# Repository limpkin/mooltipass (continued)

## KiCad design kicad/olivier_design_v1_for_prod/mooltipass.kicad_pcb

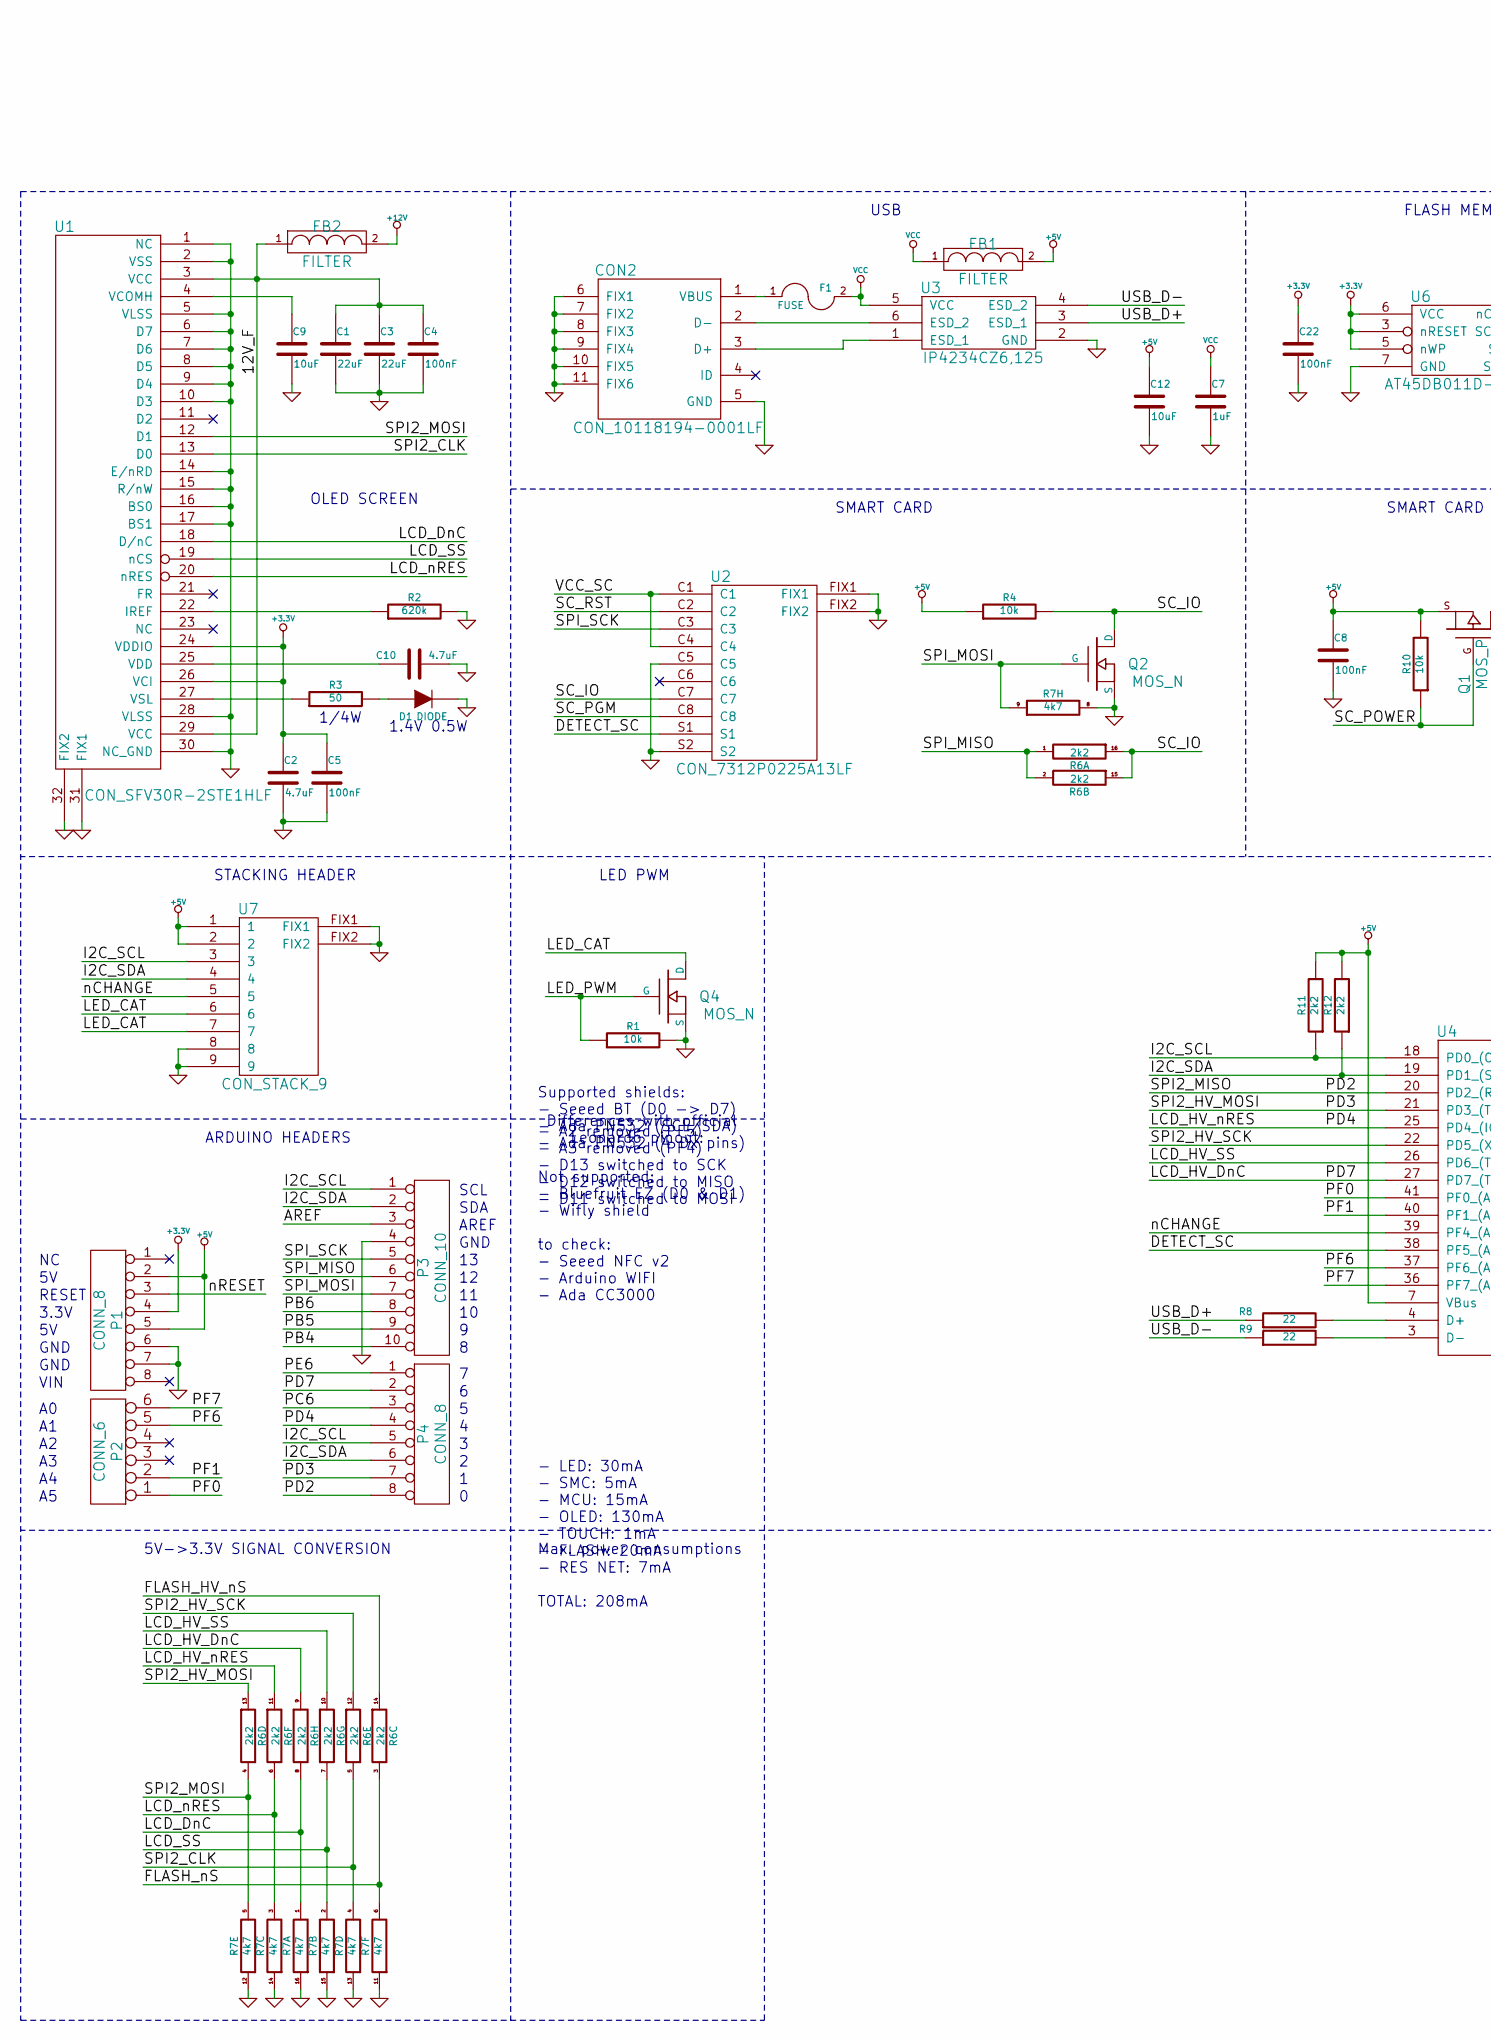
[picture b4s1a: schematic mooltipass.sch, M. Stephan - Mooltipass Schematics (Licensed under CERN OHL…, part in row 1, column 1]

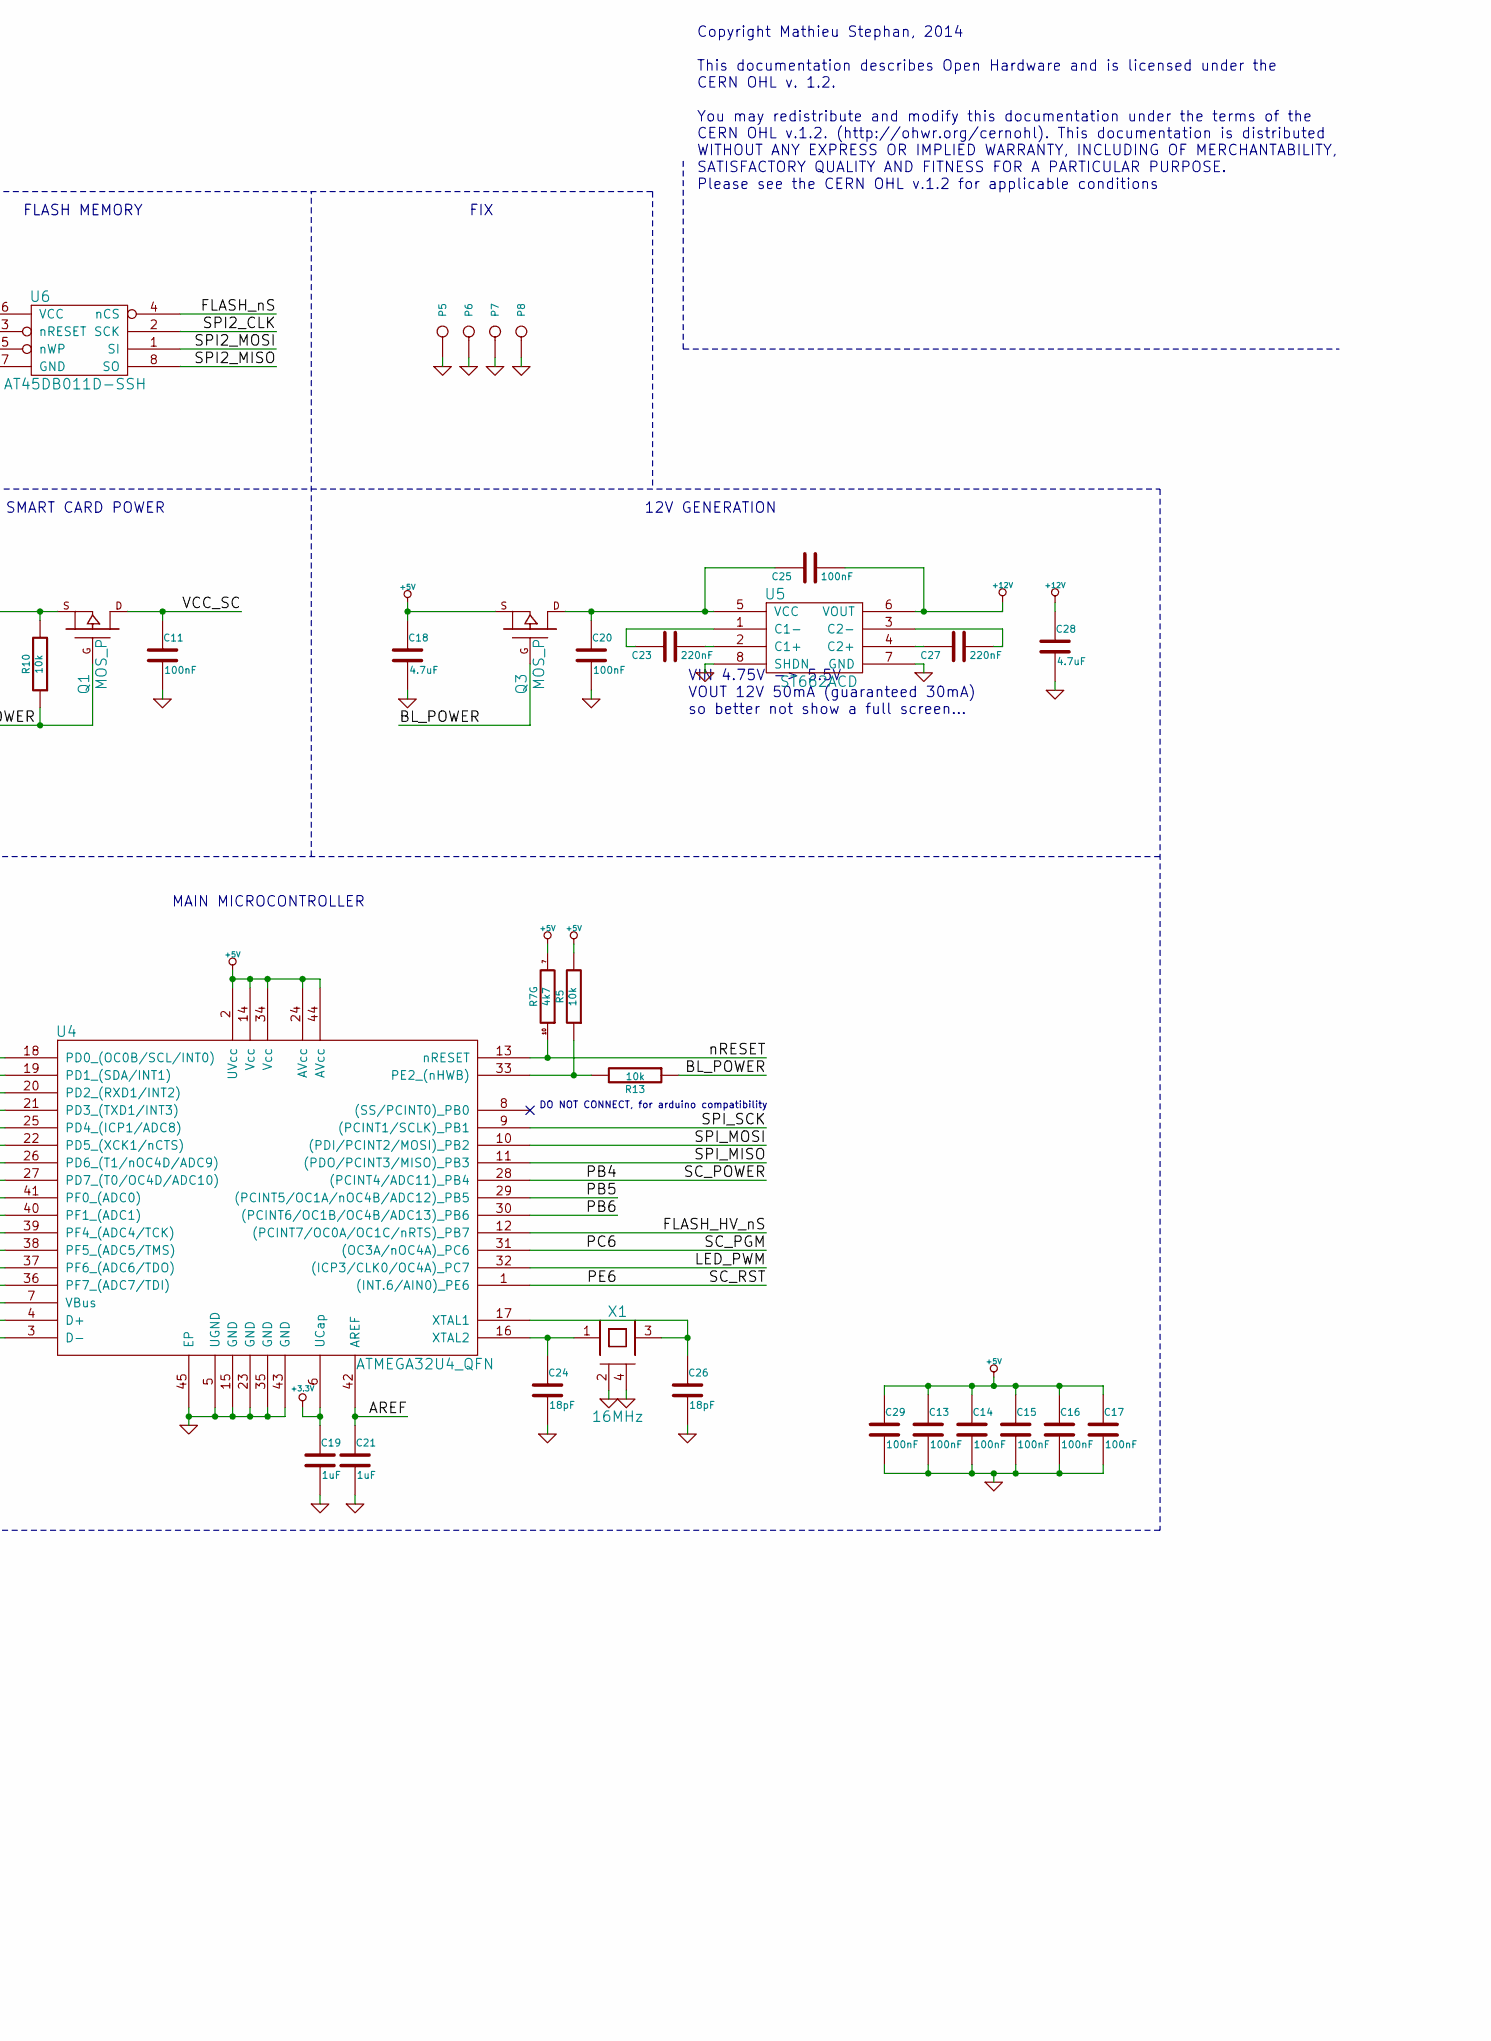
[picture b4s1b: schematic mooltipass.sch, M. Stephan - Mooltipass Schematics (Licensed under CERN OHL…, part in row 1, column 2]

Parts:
C1, C3: 22uF
C2, C10, C18, C28: 4.7uF
C4, C5, C8, C11, C13, C14, C15, C16, C17, C20, C22, C25, C29: 100nF
C7, C19, C21: 1uF
C9, C12: 10uF
C23, C27: 220nF
C24, C26: 18pF
CON2: CON_10118194-0001LF
D1: DIODE
F1: FUSE
FB1, FB2: FILTER
P1, P4: CONN_8
P2: CONN_6
P3: CONN_10
P5, P6, P7, P8: CONN_1
Q1, Q3: MOS_P
Q2, Q4: MOS_N
R1, R4, R5, R10, R13: 10k
R2: 620k
R3: 50
R6, R11, R12: 2k2
R7: 4k7
R8, R9: 22
U1: CON_SFV30R-2STE1HLF
U2: CON_7312P0225A13LF
U3: IP4234CZ6,125
U4: ATMEGA32U4_QFN
U5: ST662ACD
U6: AT45DB011D-SSH
U7: CON_STACK_9
X1: 16MHz

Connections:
+3.3V: C2.1, C5.1, C19.1, C22.1, P1.4, U1.24 (VDDIO), U1.26 (VCI), U4.6 (UCap), U6.3 (nRESET), U6.5 (nWP), U6.6 (VCC)
+5V: C8.1, C12.1, C13.1, C14.1, C15.1, C16.1, C17.1, C18.1, C29.1, FB1.2, P1.2, P1.5, Q1.S, Q3.S, R4.1, R5.2, R7.7, R10.2, R11.2, R12.2, U4.2 (UVcc), U4.7 (VBus), U4.14 (Vcc), U4.24 (AVcc), U4.34 (Vcc), U4.44 (AVcc), U7.1, U7.2
+12V: C25.2, C28.1, FB2.2, U5.6 (VOUT)
/12V_F: C1.1, C3.1, C4.1, FB2.1, U1.3 (VCC), U1.29 (VCC)
/AREF: C21.1, P3.3, U4.42 (AREF)
/BL_POWER: Q3.G, R13.1
/DETECT_SC: U2.S1, U4.38 (PF5_(ADC5/TMS))
/FLASH_HV_nS: R6.14, U4.12 ((PCINT7/OC0A/OC1C/nRTS)_PB7)
/FLASH_nS: R6.3, R7.6, U6.4 (nCS)
/I2C_SCL: P3.1, P4.5, R11.1, U4.18 (PD0_(OC0B/SCL/INT0)), U7.3
/I2C_SDA: P3.2, P4.6, R12.1, U4.19 (PD1_(SDA/INT1)), U7.4
/LCD_DnC: R6.8, R7.1, U1.18 (D/nC)
/LCD_HV_DnC: P4.2, R6.9, U4.27 (PD7_(T0/OC4D/ADC10))
/LCD_HV_SS: R6.10, U4.26 (PD6_(T1/nOC4D/ADC9))
/LCD_HV_nRES: P4.4, R6.11, U4.25 (PD4_(ICP1/ADC8))
/LCD_SS: R6.7, R7.2, U1.19 (nCS)
/LCD_nRES: R6.6, R7.3, U1.20 (nRES)
/LED_CAT: Q4.D, U7.6, U7.7
/LED_PWM: Q4.G, R1.1, U4.32 ((ICP3/CLK0/OC4A)_PC7)
/PB4: P3.10, Q1.G, R10.1, U4.28 ((PCINT4/ADC11)_PB4)
/PB5: P3.9, U4.29 ((PCINT5/OC1A/nOC4B/ADC12)_PB5)
/PB6: P3.8, U4.30 ((PCINT6/OC1B/OC4B/ADC13)_PB6)
/PC6: P4.3, U2.C8, U4.31 ((OC3A/nOC4A)_PC6)
/PD2: P4.8, U4.20 (PD2_(RXD1/INT2)), U6.8 (SO)
/PD3: P4.7, R6.13, U4.21 (PD3_(TXD1/INT3))
/PE6: P4.1, U2.C2, U4.1 ((INT.6/AIN0)_PE6)
/PF0: P2.1, U4.41 (PF0_(ADC0))
/PF1: P2.2, U4.40 (PF1_(ADC1))
/PF6: P2.5, U4.37 (PF6_(ADC6/TDO))
/PF7: P2.6, U4.36 (PF7_(ADC7/TDI))
/SC_IO: Q2.D, R4.2, R6.15, R6.16, U2.C7
/SPI2_CLK: R6.5, R7.4, U1.13 (D0), U6.2 (SCK)
/SPI2_HV_SCK: R6.12, U4.22 (PD5_(XCK1/nCTS))
/SPI2_MOSI: R6.4, R7.5, U1.12 (D1), U6.1 (SI)
/SPI_MISO: P3.6, R6.1, R6.2, U4.11 ((PDO/PCINT3/MISO)_PB3)
/SPI_MOSI: P3.7, Q2.G, R7.9, U4.10 ((PDI/PCINT2/MOSI)_PB2)
/SPI_SCK: P3.5, U2.C3, U4.9 ((PCINT1/SCLK)_PB1)
/USB_D+: R8.1, U3.3 (ESD_1)
/USB_D-: R9.1, U3.4 (ESD_2)
/VCC_SC: C11.1, Q1.D, U2.C1, U2.C4
/nCHANGE: U4.39 (PF4_(ADC4/TCK)), U7.5
/nRESET: P1.3, R7.10, U4.13 (nRESET)
GND: C1.2, C2.2, C3.2, C4.2, C5.2, C7.2, C8.2, C9.2, C10.2, C11.2, C12.2, C13.2, C14.2, C15.2, C16.2, C17.2, C18.2, C19.2, C20.2, C21.2, C22.2, C24.2, C26.2, C28.2, C29.2, CON2.5 (GND), CON2.6 (FIX1), CON2.7 (FIX2), CON2.8 (FIX3), CON2.9 (FIX4), CON2.10 (FIX5), CON2.11 (FIX6), D1.2 (K), P1.6, P1.7, P3.4, P5.1, P6.1, P7.1, P8.1, Q2.S, Q4.S, R1.2, R2.2, R7.8, R7.11, R7.12, R7.13, R7.14, R7.15, R7.16, U1.1 (NC), U1.2 (VSS), U1.5 (VLSS), U1.6 (D7), U1.7 (D6), U1.8 (D5), U1.9 (D4), U1.10 (D3), U1.14 (E/nRD), U1.15 (R/nW), U1.16 (BS0), U1.17 (BS1), U1.28 (VLSS), U1.30 (NC_GND), U1.31 (FIX1), U1.32 (FIX2), U2.C5, U2.FIX1, U2.FIX2, U2.S2, U3.2 (GND), U4.5 (UGND), U4.15 (GND), U4.23 (GND), U4.35 (GND), U4.43 (GND), U4.45 (EP), U5.7 (GND), U5.8 (SHDN), U6.7 (GND), U7.8, U7.9, U7.FIX1, U7.FIX2, X1.2, X1.4
unnamed: R3.1, U1.27 (VSL)
unnamed: C10.1, U1.25 (VDD)
unnamed: R2.1, U1.22 (IREF)
unnamed: C9.1, U1.4 (VCOMH)
unnamed: C26.1, U4.17 (XTAL1), X1.3
unnamed: C24.1, U4.16 (XTAL2), X1.1
unnamed: D1.1 (A), R3.2
unnamed: C27.2, U5.3 (C2-)
unnamed: C20.1, C25.1, Q3.D, U5.5 (VCC)
unnamed: C27.1, U5.4 (C2+)
unnamed: C23.2, U5.2 (C1+)
unnamed: C23.1, U5.1 (C1-)
unnamed: CON2.1 (VBUS), F1.1
unnamed: R5.1, R13.2, U4.33 (PE2_(nHWB))
unnamed: CON2.3 (D+), U3.1 (ESD_1)
unnamed: CON2.2 (D-), U3.6 (ESD_2)
unnamed: R8.2, U4.4 (D+)
unnamed: R9.2, U4.3 (D-)
VCC: C7.1, F1.2, FB1.1, U3.5 (VCC)

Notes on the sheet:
1/4W
1.4V 0.5W
VIN 4.75V -> 5.5V VOUT 12V 50mA (guaranteed 30mA) so better not show a full screen...
DO NOT CONNECT, for arduino compatibility
Copyright Mathieu Stephan, 2014 This documentation describes Open Hardware and is licensed under the CERN OHL v. 1.2. You may redistribute and modify this documentation under the terms of the CERN OHL v.1.2. (http://ohwr.org/cernohl). This documentation is distributed WITHOUT ANY EXPRESS OR IMPLIED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
USB
SMART CARD
SMART CARD POWER
OLED SCREEN
12V GENERATION
FLASH MEMORY
STACKING HEADER
SCL
SDA
AREF
GND
RESET
3.3V
VIN
ARDUINO HEADERS
LED PWM
Supported shields: - Seeed BT (D0 -> D7) - Ada PN532 (SCL/SDA) - Ada PN532 (4 Dx pins) Not supported: - Bluefruit EZ (D0 & D1) - Wifly shield to check: - Seeed NFC v2 - Arduino WIFI - Ada CC3000
FIX
Differences with official Leonardo pinout:
- A2 removed (PF5) - A3 removed (PF4) - D13 switched to SCK - D12 switched to MISO - D11 switched to MOSI
5V->3.3V SIGNAL CONVERSION
MAIN MICROCONTROLLER
Max. power consumptions
- LED: 30mA - SMC: 5mA - MCU: 15mA - OLED: 130mA - TOUCH: 1mA - FLASH: 20mA - RES NET: 7mA TOTAL: 208mA

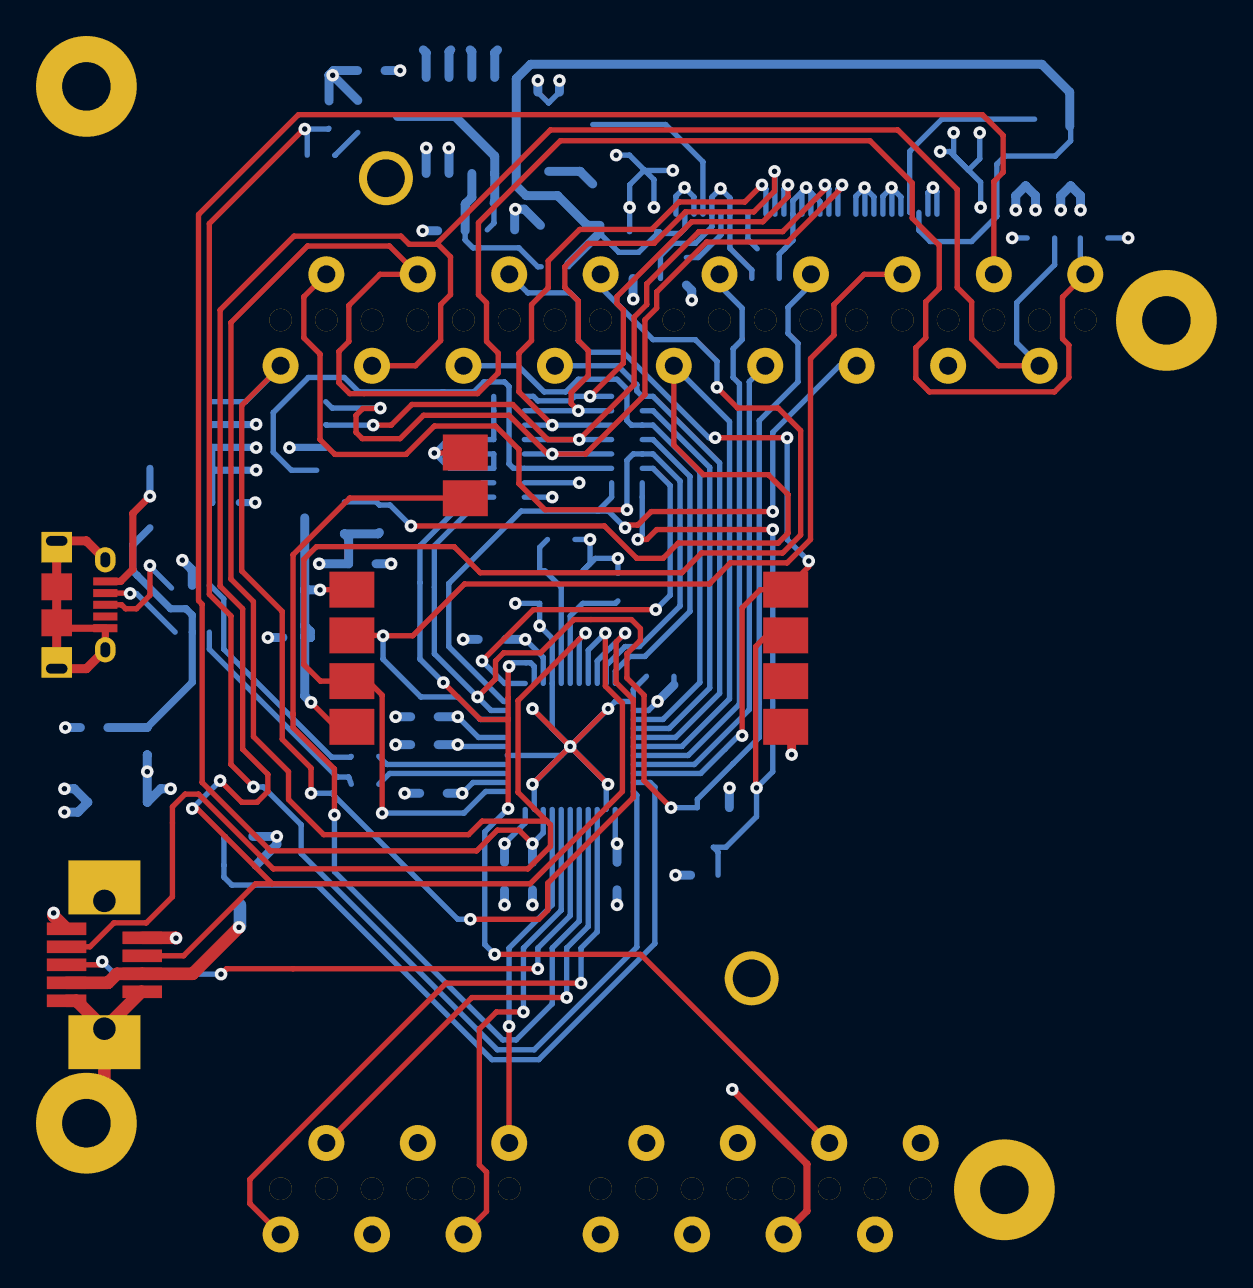
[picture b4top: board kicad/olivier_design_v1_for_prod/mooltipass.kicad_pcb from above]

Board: 4 copper layers, 66 parts (0 on the bottom side), 62 nets.

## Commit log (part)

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2017-07-04 [ci skip] test
2017-07-04 test trigger travis
2017-07-04 test [ci-ext] trigger
2017-07-05 udpated readme
2017-07-05 added public restricted mode
2017-07-07 handle http auth
2017-07-07 [ci-ext] CI trigger
2017-07-10 allowing chrome app to import moolticute export files
2017-07-10 don't override credentialsCache with empty value
2017-07-10 [ci-ext] recategorizing CI tests
2017-07-10 [ci-ext] bug fix for ebay ci testing
2017-07-11 revisited submit and missing form data
2017-07-11 [ci-ext] be less restrictive to send post_detected event when a post is detected
2017-07-12 don't treat link as submit button and delay before submitting form
2017-07-12 [ci-ext] lower case m for microspot credentials
2017-07-12 button selectors priority
2017-07-14 make it pretty
2017-07-14 ignore links for password restore
2017-07-14 remerge with master
2017-07-14 [ci-ext] moving websites in features to reflect their supported status
2017-07-16 Extend functionality to fix Trillian login
2017-07-16 Disable emulation mode
2017-07-16 Normalize usage of messaging
2017-07-17 update instructions
2017-07-17 ignore pattern for paypal
2017-07-17 replace font icon with inlined svg
2017-07-17 consider every url as valid
2017-07-17 url validation exception for localhost
2017-07-17 [ci-ext] correcting @reepush 's mistakes
2017-07-17 improved and final wheel jitter solving code
2017-07-18 [ci-ext] added steampowered password for CI
2017-07-18 don't initialize in user targeting iframes
2017-07-18 added support for steam
2017-07-18 [ci-ext] ci trigger for steam
2017-07-20 trigger submit event for steam and ignore wrong submit button
2017-07-20 do not autosubmit form with two-factor auth for Steam
2017-07-20 steam password
2017-07-20 change z-index for password generation overlay
2017-07-21 fix password popover position
2017-07-21 [ci-ext] correct callback in case a website is blacklisted
2017-07-21 make tests less verbose
2017-07-21 mac compatibility fixes
2017-07-21 wrong detection of two page auth
2017-07-21 mark protonmail test as supported
2017-07-21 info about testing locally on macos
2017-07-21 remove mac compatibility for sed, update readme
2017-07-21 [ci-ext] reverting travis.yml for scripts
2017-07-21 [ci-ext] recategorizing patreon due to captcha
2017-07-22 fixed anibis and github
2017-07-22 fixed hackaday
2017-07-24 new combination "Login Form with Text and Search field"
2017-07-24 evernote combination
2017-07-24 prioritize div with onclick attribute
2017-07-25 cancel first http auth request
2017-07-25 allow input with type=login
2017-07-25 rearrange tests
2017-07-26 new feature define: pin for administrative functions (WIP)
2017-07-26 compatibility with ldlc.ch and techmania.ch
2017-07-26 Revert "rearrange tests"
    This reverts commit a5b50cb55cc29a2a6cd223371435c4f126fff1c5.
2017-07-26 show notice with hostname
2017-07-26 [ci-ext] ci trigger to check failure
2017-07-28 pass http auth parameters in location
2017-07-28 sites compatibility * minfin.com.ua * pc-ostschweiz.ch * tripadvisor.com * chipdirect.com
2017-07-28 update access key
2017-07-28 MICROCHIPPASS
2017-07-29 new define to left align credentials in login & favorite menu
2017-07-31 handle submit event on submit button click
2017-07-31 improved detectSubmitButton
2017-07-31 handle special cases
2017-08-01 fix multiple iframes issue
2017-08-01 keypress to keydown, change selector priority
2017-08-01 change button selectors
2017-08-01 .sh script to include http auth
2017-08-02 info about submit interception
2017-08-02 trigger change event for react inputs
2017-08-03 [ci-ext] recategorizing features, extension version bump
2017-08-03 [ci-ext] updated travis.yml
2017-08-05 fixed techmania
2017-08-05 fixed minfin
2017-08-05 Tripadivisor fixed
2017-08-06 fixed esp
2017-08-06 [ci-ext] recategorizing for CI
2017-08-06 extend selector for login form mixed combination
2017-08-06 enable debugging in firefox
2017-08-06 fixed gmail and anibis
2017-08-06 fixed airbnb
2017-08-06 added turkish arilines
2017-08-06 observe new fields based on type change also
2017-08-06 extended password selector for mixed combination
2017-08-06 airbnb password
2017-08-06 turkish pass
2017-08-07 add vmbuild to local domain
2017-08-07 cancel requests which are initiated not from tabs
2017-08-07 initial UI in iframes support
2017-08-07 remove unused bootstrap-btn.css
2017-08-07 remove unused popups
2017-08-07 [ci-ext] ci trigger and update to readme
2017-08-07 [ci-ext] recategorizing ci websites
2017-08-08 chrome is undefined in Safari
2017-08-08 adjust icon position
2017-08-09 different field for two-factor auth for Steam with mobile code
2017-08-09 working password dialog
2017-08-09 [ci-ext] ci trigger for metacritic
2017-08-10 custom credentials selection overlay in iframe
2017-08-11 working custom credentials selection
2017-08-11 fix race condition between mccombs and cipFields for unique id
2017-08-14 relative icon positioning
2017-08-14 password dialog with foundation
2017-08-14 high resolution icon
2017-08-14 allow to select already selected fields
2017-08-14 cancel button for custom fields selection
2017-08-15 align login input in password dialog
2017-08-15 password dialog padding
2017-08-15 small UI improvements
2017-08-15 fading dialog
2017-08-15 shadows for buttons
2017-08-15 highlight mcCombs fields
2017-08-15 parameters for ui elements
2017-08-16 check if username field is available
2017-08-16 check that containerForm exists
2017-08-16 http auth in ui
2017-08-16 fadein on iframe load
2017-08-16 consider margin for icon position
2017-08-16 check for fields
2017-08-16 autofocus for login
2017-08-16 fixed width for popup
2017-08-16 disable user select for fields selection
2017-08-18 invert gradient direction for password dialog
2017-08-18 allow local domains
2017-08-19 fixed dropbox and komoot
2017-08-21 check for dialog on hide and on selection show, pass window dimensions
2017-08-21 update jquery
2017-08-21 trigger change event after filling password fields
2017-08-21 consider input wit tel type as login field
2017-08-21 don't focus password dialog toggle on tab
2017-08-21 bind currentForm for keydown
2017-08-21 prioritize selector for vudu.com
2017-08-22 remove wide matching div selector
2017-08-22 remove special characters from id
2017-08-22 soundcloud extended combination
2017-08-22 ignore facebook and google auth
2017-08-22 extend password selector with realtype attribute
2017-08-23 improved submit button detection
2017-08-23 ignore aria-hidden elements, extend submit button selectors
2017-08-23 trigger mcCombs to re-evaluate combinations after credentials selection
2017-08-23 extend ACCEPT_PATTERNS
2017-08-23 extend input selector with name=username
2017-08-24 remove sendkeys in login for trillian support
2017-08-24 remove ignore patternt for americanexpress.com
2017-08-24 prioritize password field for submit button detection over username field
2017-08-24 captcha detection
2017-08-25 button selector and accept pattern for changing password in google
2017-08-25 skip special combination for evernote's password restore form
2017-08-25 exception icloud auth iframe
2017-08-25 [ci-ext] removing obsolete automated test folder
2017-08-26 extension version bump
2017-08-26 fixed github
2017-08-26 microspot password update
2017-08-26 fixed microspot
2017-08-28 safari compatibility
2017-08-29 algorithm redesign for scroll wheel problems
2017-08-29 remove contentSettings permission
2017-09-01 missed closing bracket
2017-09-12 support tab focus and close event in Safari
2017-09-13 don't show notifications for Safari
2017-09-13 fix Firefox notification issues
2017-09-13 chrome extension version bump
2017-09-18 ignore pattern for westernunion.com
2017-10-04 click on input caused exception in firefox
2017-10-04 enable development logs only in chrome
2017-10-04 wrap click on password field in try / catch block
2017-10-04 accept pattern for ironmountainsupplies.co.uk
2017-10-04 ignore pattern for applic8.hr-cloud.com
2017-10-06 ignore header link clicks on github.com
2017-10-06 ignore password lost link for gandi.net
2017-10-12 hide custom credentials for two page auth
2017-10-12 reenable notifications when device is connected
2017-10-12 overflow password dialog
2017-10-12 reenable notifications on status change
2017-10-12 overflow dialog fix
2017-10-12 remove timeout
2017-10-13 disable custom fields in popup status
2017-10-24 ignore password fields with tabindex=-1
2017-10-24 citi.com combination
2017-10-24 make sure that password dialog doesn't exeed iframe boundaries
2017-10-26 check for captcha visibility
2017-10-26 hsbc.com combination
2017-10-27 fixed eBay
2017-10-27 [ci-ext] ci update
2017-10-28 [ci-ext]ci trigger
2017-11-14 ignore pattern for catalogue.bm-lyon.fr
2017-11-14 trigger blur on fields
2017-11-14 http auth caution
2017-11-14 improved custom credentials selection
2017-11-14 reset triangle position
2017-11-14 upwork.com compatibility
2017-11-14 norwegian.com compatibility
2017-11-16 reset detected forms, log submit button
2017-11-22 advanzia.com compatibility
2017-11-22 align heading
2017-11-22 check request type for http auth
2017-11-24 spotify.com compatibility
2017-12-02 portuguese keyboard layout
2017-12-08 wasabisys.com compatibility
2017-12-11 ignore mailformed action for form
2017-12-11 compatibility with ims.brk.de
2017-12-11 allow iframe for chase.com
2017-12-13 make defined credentials work
2017-12-13 special combination for pwc.com
2017-12-13 extend selectors for username custom field
2017-12-13 disable emulation
2017-12-13 remove markAllStringFields
2017-12-19 ignore submit button if it's far than 150px from input
2017-12-19 update username field only when it's undefined for mixed form combination
2017-12-19 pick and place files
2017-12-19 changing the way the keypress delay is done
2017-12-20 add bootloader.hex
2017-12-20 compare only vertical distance between input and submit button
2017-12-20 accept pattern for banquepopulaire.fr
2017-12-22 check field visibility for two step auth
2018-01-02 fixed config error [ci-ext]
2018-01-15 update link to Mooltipass Mini
    The description talks about Mooltipass Mini but the link leads to the regular Mooltipass. I have updated the link for consistency.
2018-01-28 prevent showing icon if password field is less than 100px by width
2018-01-28 check for viewport size to prevent iframe init
2018-01-28 disabled autosubmit for gls-online-filiale.de
2018-01-29 login icon
2018-01-30 support old safari
2018-02-13 Adding french mini user manual
2018-02-14 extension migrated to new repo
2018-03-31 [docs] - Mooltipass Project Repository - README.md - Fixing Minor Grammar Issues
    #### [docs] - Mooltipass Project Repository - README.md - Fixing Minor Grammar Issues
2018-06-13 DK map
2018-06-13 mac dk bundle
2018-08-27 new alt keymaps
2018-09-29 ca_fr keymap
2018-09-29 name change
2019-03-29 latest changes
2019-03-29 contents hiding feature check on smartcard
2019-03-29 added new solution for fw update
2019-05-10 missing function call
2019-07-27 unused bitmaps
2019-07-27 font generation script: option to add pix complement
2019-07-28 new bundle with extra keyboard maps
2019-08-07 CVE-2019-14357 statement
2019-10-30 Bump ffi from 1.9.6 to 1.11.1 in /chrome_app/html
    Bumps [ffi](https://github.com/ffi/ffi) from 1.9.6 to 1.11.1.
    - [Release notes](https://github.com/ffi/ffi/releases)
    - [Changelog](https://github.com/ffi/ffi/blob/master/CHANGELOG.md)
    - [Commits](https://github.com/ffi/ffi/compare/v1.9.6...1.11.1)
2020-07-17 updated decoding tool
2020-10-13 Bump junit from 4.12 to 4.13.1 in /sauce_labs_tests
    Bumps [junit](https://github.com/junit-team/junit4) from 4.12 to 4.13.1.
    - [Release notes](https://github.com/junit-team/junit4/releases)
    - [Changelog](https://github.com/junit-team/junit4/blob/main/doc/ReleaseNotes4.12.md)
    - [Commits](https://github.com/junit-team/junit4/compare/r4.12...r4.13.1)
2021-04-26 Bump commons-io from 2.5 to 2.7 in /sauce_labs_tests
    Bumps commons-io from 2.5 to 2.7.
